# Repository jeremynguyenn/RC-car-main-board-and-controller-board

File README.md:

| Control Board
 | Main RC board

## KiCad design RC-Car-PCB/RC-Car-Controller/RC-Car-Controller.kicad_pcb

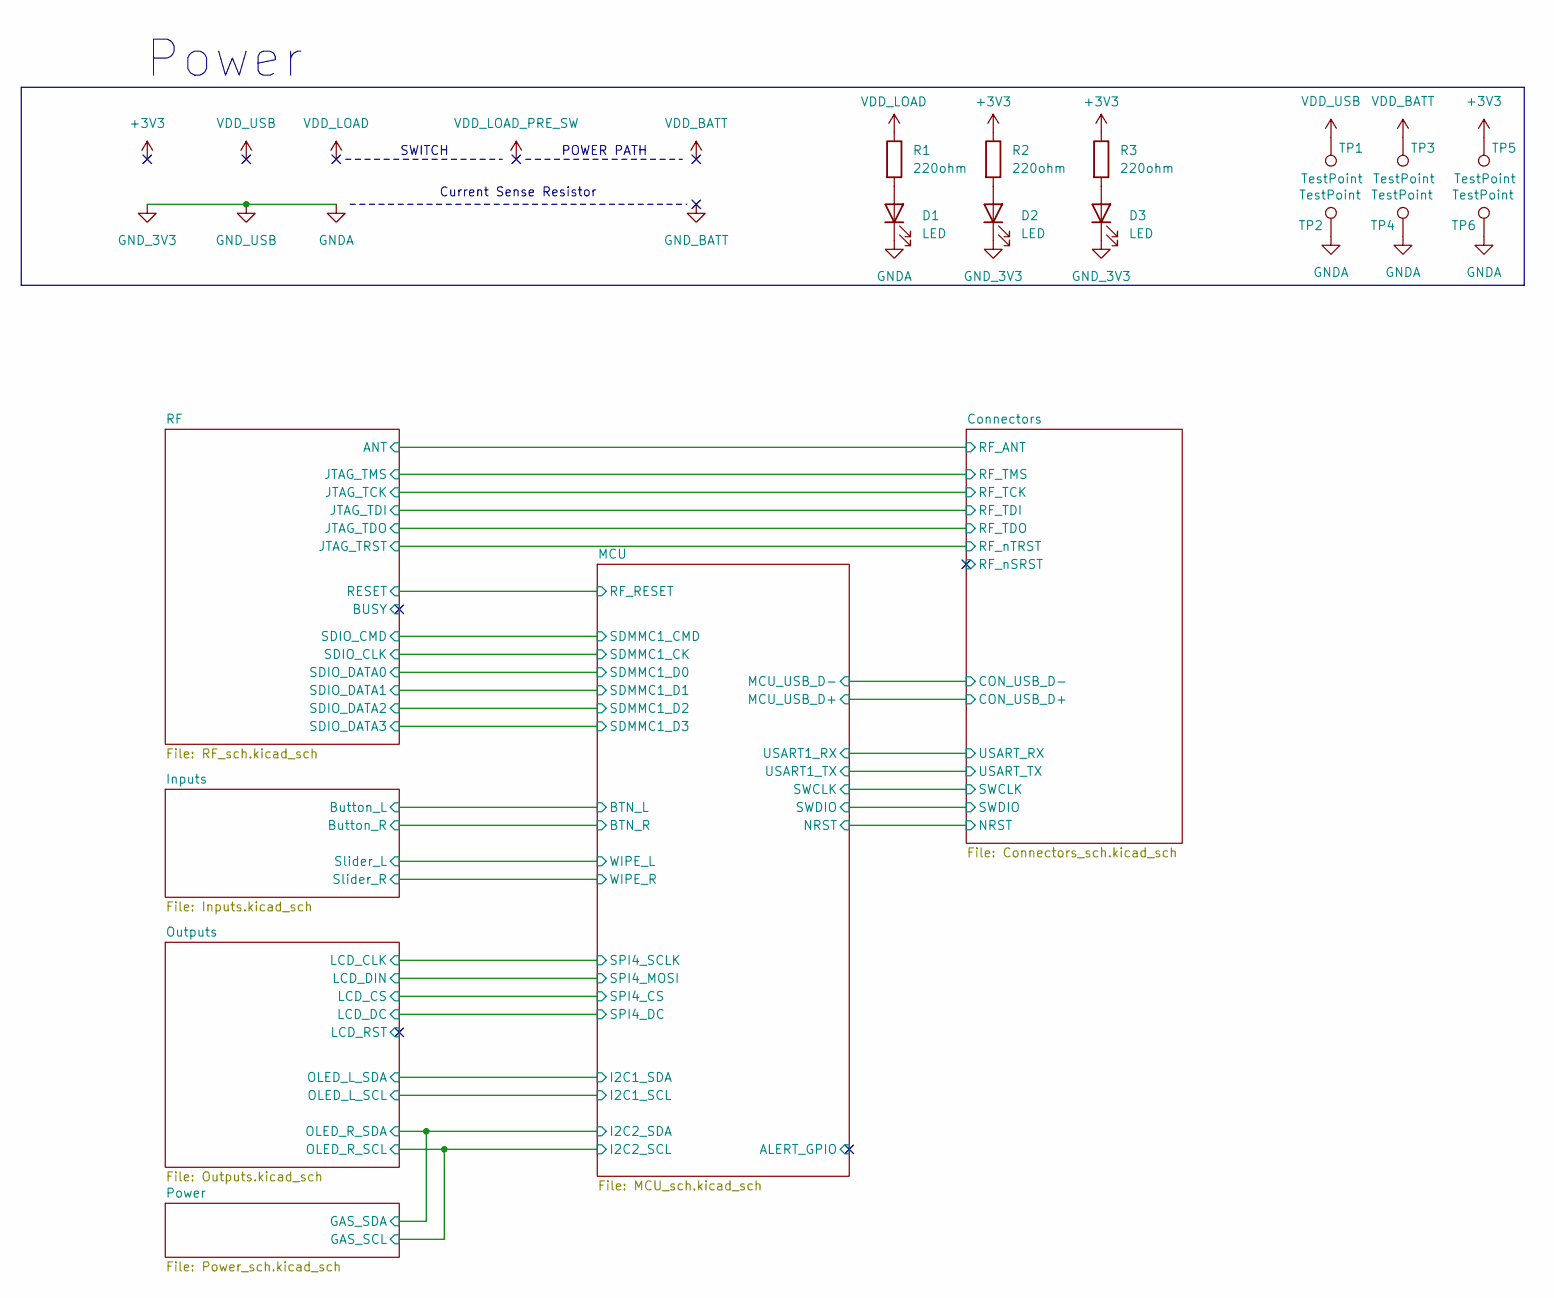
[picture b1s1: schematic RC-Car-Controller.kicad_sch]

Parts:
D1, D2: LED; LED_0603_1608Metric; MANUF_PN LTST-C190GKT
D3: LED; LED_D5.0mm; MANUF_PN LTL-4293
R1, R2, R3: 220ohm; R_0603_1608Metric; MANUF_PN RMCF0603FT220R
TP1, TP2, TP3, TP4, TP5, TP6: TestPoint; PinHeader_1x02_P2.54mm_Vertical; MANUF_PN N/A

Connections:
+3V3: R2.1, R3.1, TP5.1; also elsewhere on the board
GNDA: D1.1 (K), D2.1 (K), D3.1 (K), TP2.1, TP4.1, TP6.1; also elsewhere on the board
unnamed: D1.2 (A), R1.2
unnamed: D2.2 (A), R2.2
unnamed: D3.2 (A), R3.2
VDD_BATT: TP3.1; also elsewhere on the board
VDD_LOAD: R1.1; also elsewhere on the board
VDD_USB: TP1.1; also elsewhere on the board

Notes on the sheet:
Power
POWER PATH
Current Sense Resistor
SWITCH

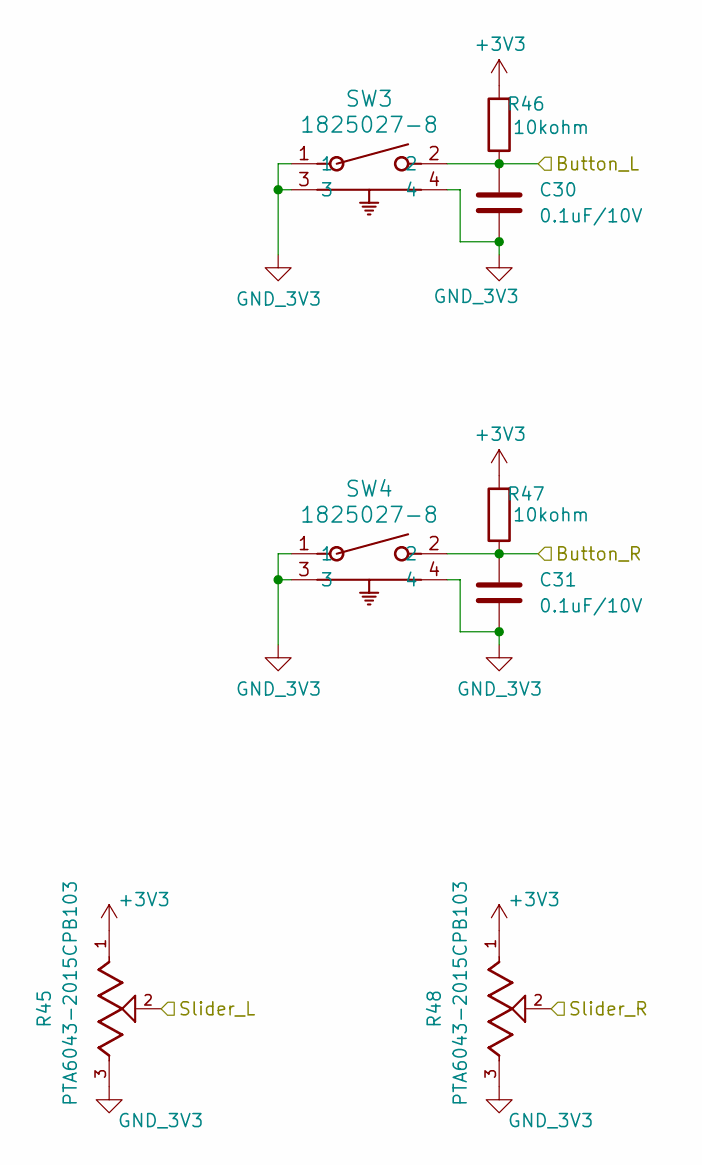
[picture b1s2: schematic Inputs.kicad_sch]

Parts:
C30, C31: 0.1uF/10V; C_0603_1608Metric; MANUF_PN C0603C104K5RAC7411
R45, R48: PTA6043-2015CPB103; Potentiometer_Bourns_PTA6043_Single_Slide; MANUF_PN PTA6043-2015CPB103
R46, R47: 10kohm; C_0603_1608Metric; MANUF_PN RC0603FR-0710KL
SW3, SW4: 1825027-8; SW2_1825027-C_TEC; MANUF_PN 1825027-8

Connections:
+3V3: R45.1, R46.2, R47.2, R48.1; also elsewhere on the board
/Inputs/Button_L: C30.1, R46.1, SW3.2; also elsewhere on the board
/Inputs/Button_R: C31.1, R47.1, SW4.2; also elsewhere on the board
/Inputs/Slider_L: R45.2; also elsewhere on the board
/Inputs/Slider_R: R48.2; also elsewhere on the board
GNDA: C30.2, C31.2, R45.3, R48.3, SW3.1, SW3.3, SW3.4, SW4.1, SW4.3, SW4.4; also elsewhere on the board

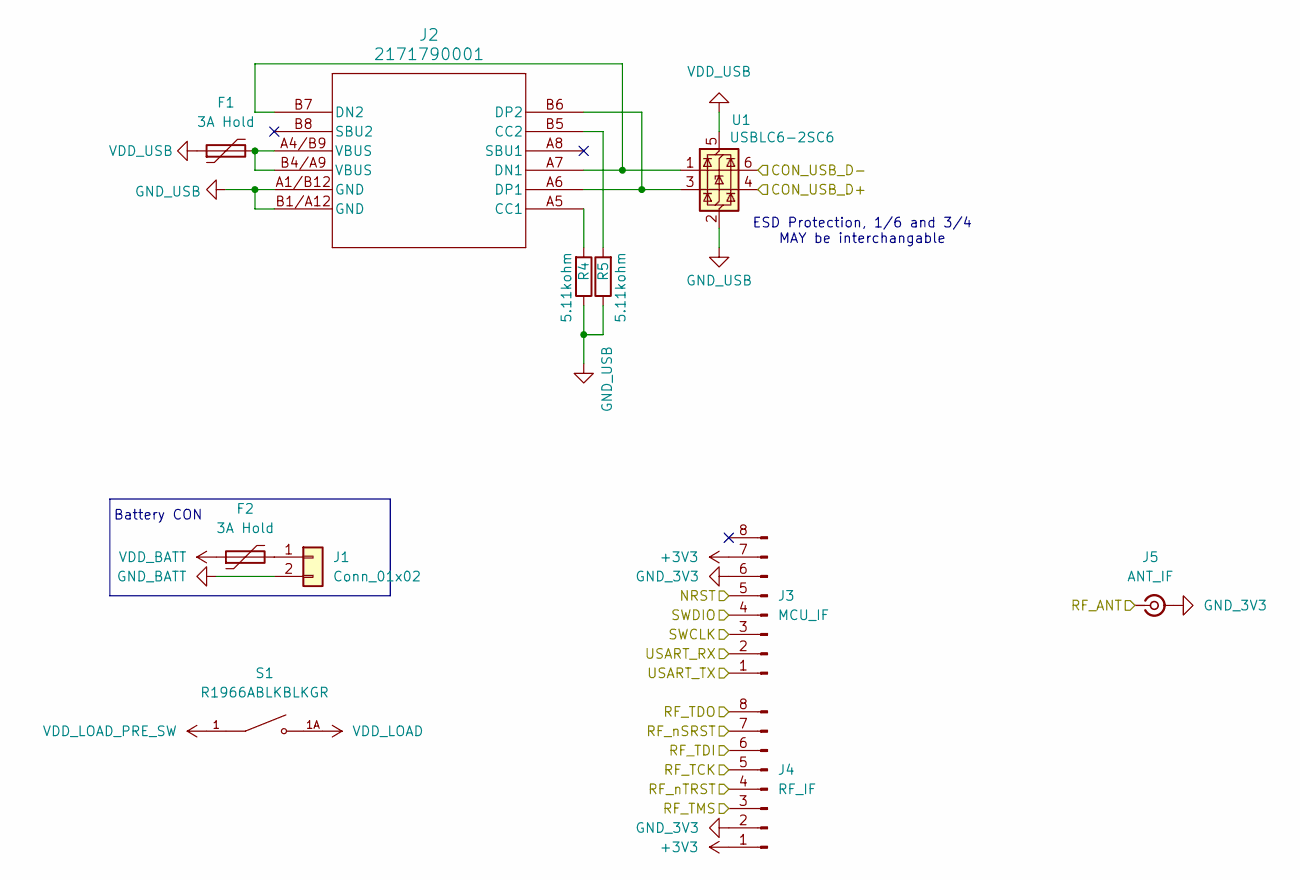
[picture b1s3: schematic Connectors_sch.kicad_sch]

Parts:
F1, F2: 3A Hold; Fuse_1812_4532Metric_Pad1.30x3.40mm_HandSolder; MANUF_PN 0ZCG0300FF2B
J1: Conn_01x02; JST_XH_B2B-XH-AM_1x02_P2.50mm_Vertical; MANUF_PN B2B-XH-AM
J2: 2171790001; 2171790001_MOL; MANUF_PN 2171790001
J3: MCU_IF; PinHeader_2x04_P2.54mm_Vertical; MANUF_PN PH2-08-UA
J4: RF_IF; PinHeader_2x04_P2.54mm_Vertical; MANUF_PN PH2-08-UA
J5: ANT_IF; SMA_Molex_73251-1153_EdgeMount_Horizontal; MANUF_PN 0732511153
R4, R5: 5.11kohm; R_0603_1608Metric; MANUF_PN CRCW06035K11FKEAC
S1: R1966ABLKBLKGR; SW_R1966ABLKBLKGR; PARTREV E
U1: USBLC6-2SC6; SOT-23-6; MANUF_PN USBLC6-2SC6

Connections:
+3V3: J3.7, J4.1; also elsewhere on the board
/Connectors/CON_USB_D+: U1.4 (I/O2); also elsewhere on the board
/Connectors/CON_USB_D-: U1.6 (I/O1); also elsewhere on the board
/Connectors/NRST: J3.5; also elsewhere on the board
/Connectors/RF_ANT: J5.1 (In); also elsewhere on the board
/Connectors/RF_TCK: J4.5; also elsewhere on the board
/Connectors/RF_TDI: J4.6; also elsewhere on the board
/Connectors/RF_TDO: J4.8; also elsewhere on the board
/Connectors/RF_TMS: J4.3; also elsewhere on the board
/Connectors/RF_nSRST: J4.7
/Connectors/RF_nTRST: J4.4; also elsewhere on the board
/Connectors/SWCLK: J3.3; also elsewhere on the board
/Connectors/SWDIO: J3.4; also elsewhere on the board
/Connectors/USART_RX: J3.2; also elsewhere on the board
/Connectors/USART_TX: J3.1; also elsewhere on the board
GNDA: J2.A1/B12 (GND), J2.B1/A12 (GND), J3.6, J4.2, J5.2 (Ext), R4.1, R5.1, U1.2 (GND); also elsewhere on the board
GND_BATT: J1.2; also elsewhere on the board
unnamed: F1.2, J2.A4/B9 (VBUS), J2.B4/A9 (VBUS)
unnamed: F2.2, J1.1
unnamed: J2.A5 (CC1), R4.2
unnamed: J2.B5 (CC2), R5.2
unnamed: J2.A7 (DN1), J2.B7 (DN2), U1.1 (I/O1)
unnamed: J2.A6 (DP1), J2.B6 (DP2), U1.3 (I/O2)
VDD_BATT: F2.1; also elsewhere on the board
VDD_LOAD: S1.1A; also elsewhere on the board
VDD_LOAD_PRE_SW: S1.1; also elsewhere on the board
VDD_USB: F1.1, U1.5 (VBUS); also elsewhere on the board

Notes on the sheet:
Battery CON
ESD Protection, 1/6 and 3/4 MAY be interchangable

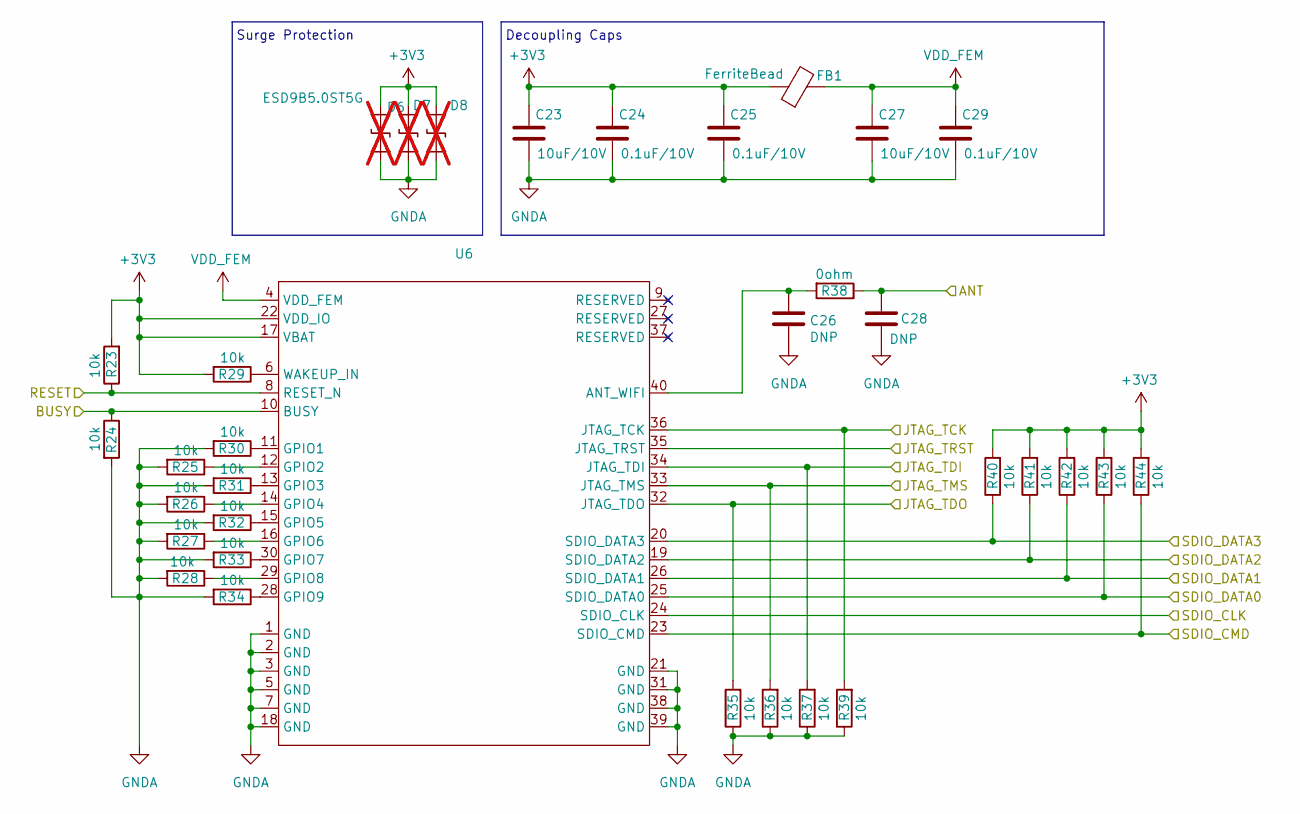
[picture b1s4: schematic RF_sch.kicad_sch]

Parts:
C23, C27: 10uF/10V; C_0603_1608Metric; MANUF_PN CL10A106KP8NNNC
C24, C25, C29: 0.1uF/10V; C_0603_1608Metric; MANUF_PN C0603C104K5RAC7411
C26, C28: DNP; C_0603_1608Metric; MANUF_PN N/A
D6, D7, D8: ESD9B5.0ST5G; D_SOD-923; MANUF_PN ESD9B5.0ST5G; not fitted
FB1: FerriteBead; C_0603_1608Metric; MANUF_PN HCB 1608KF-181T20
R23, R24, R25, R26, R27, R28, R29, R30, R31, R32, R33, R34, R35, R36, R37, R39, R40, R41, R42, R43, R44: 10k; C_0603_1608Metric; MANUF_PN RC0603FR-0710KL
R38: 0ohm; R_0603_1608Metric; MANUF_PN RMCF0603ZT0R00
U6: FGH100MABMD; MANUF_PN FGH100MABMD

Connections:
+3V3: C23.1, C24.1, C25.1, D6.2 (A2), D7.2 (A2), D8.2 (A2), FB1.1, R23.2, R29.2, R40.2, R41.2, R42.2, R43.2, R44.2, U6.17 (VBAT), U6.22 (VDD_IO); also elsewhere on the board
/Connectors/RF_ANT: C28.1, R38.1; also elsewhere on the board
/Connectors/RF_TCK: R39.2, U6.36 (JTAG_TCK); also elsewhere on the board
/Connectors/RF_TDI: R37.2, U6.34 (JTAG_TDI); also elsewhere on the board
/Connectors/RF_TDO: R35.2, U6.32 (JTAG_TDO); also elsewhere on the board
/Connectors/RF_TMS: R36.2, U6.33 (JTAG_TMS); also elsewhere on the board
/Connectors/RF_nTRST: U6.35 (JTAG_TRST); also elsewhere on the board
/MCU/RF_RESET: R23.1, U6.8 (RESET_N); also elsewhere on the board
/MCU/SDMMC1_CK: U6.24 (SDIO_CLK); also elsewhere on the board
/MCU/SDMMC1_CMD: R44.1, U6.23 (SDIO_CMD); also elsewhere on the board
/MCU/SDMMC1_D0: R43.1, U6.25 (SDIO_DATA0); also elsewhere on the board
/MCU/SDMMC1_D1: R42.1, U6.26 (SDIO_DATA1); also elsewhere on the board
/MCU/SDMMC1_D2: R41.1, U6.19 (SDIO_DATA2); also elsewhere on the board
/MCU/SDMMC1_D3: R40.1, U6.20 (SDIO_DATA3); also elsewhere on the board
/RF/BUSY: R24.1, U6.10 (BUSY)
GNDA: C23.2, C24.2, C25.2, C26.2, C27.2, C28.2, C29.2, D6.1 (A1), D7.1 (A1), D8.1 (A1), R24.2, R25.2, R26.2, R27.2, R28.2, R30.2, R31.2, R32.2, R33.2, R34.2, R35.1, R36.1, R37.1, R39.1, U6.1 (GND), U6.2 (GND), U6.3 (GND), U6.5 (GND), U6.7 (GND), U6.18 (GND), U6.21 (GND), U6.31 (GND), U6.38 (GND), U6.39 (GND); also elsewhere on the board
unnamed: C26.1, R38.2, U6.40 (ANT_WIFI)
unnamed: R30.1, U6.11 (GPIO1)
unnamed: R25.1, U6.12 (GPIO2)
unnamed: R31.1, U6.13 (GPIO3)
unnamed: R26.1, U6.14 (GPIO4)
unnamed: R32.1, U6.15 (GPIO5)
unnamed: R27.1, U6.16 (GPIO6)
unnamed: R33.1, U6.30 (GPIO7)
unnamed: R28.1, U6.29 (GPIO8)
unnamed: R34.1, U6.28 (GPIO9)
unnamed: R29.1, U6.6 (WAKEUP_IN)
VDD_FEM: C27.1, C29.1, FB1.2, U6.4 (VDD_FEM)

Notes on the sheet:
Decoupling Caps
Surge Protection

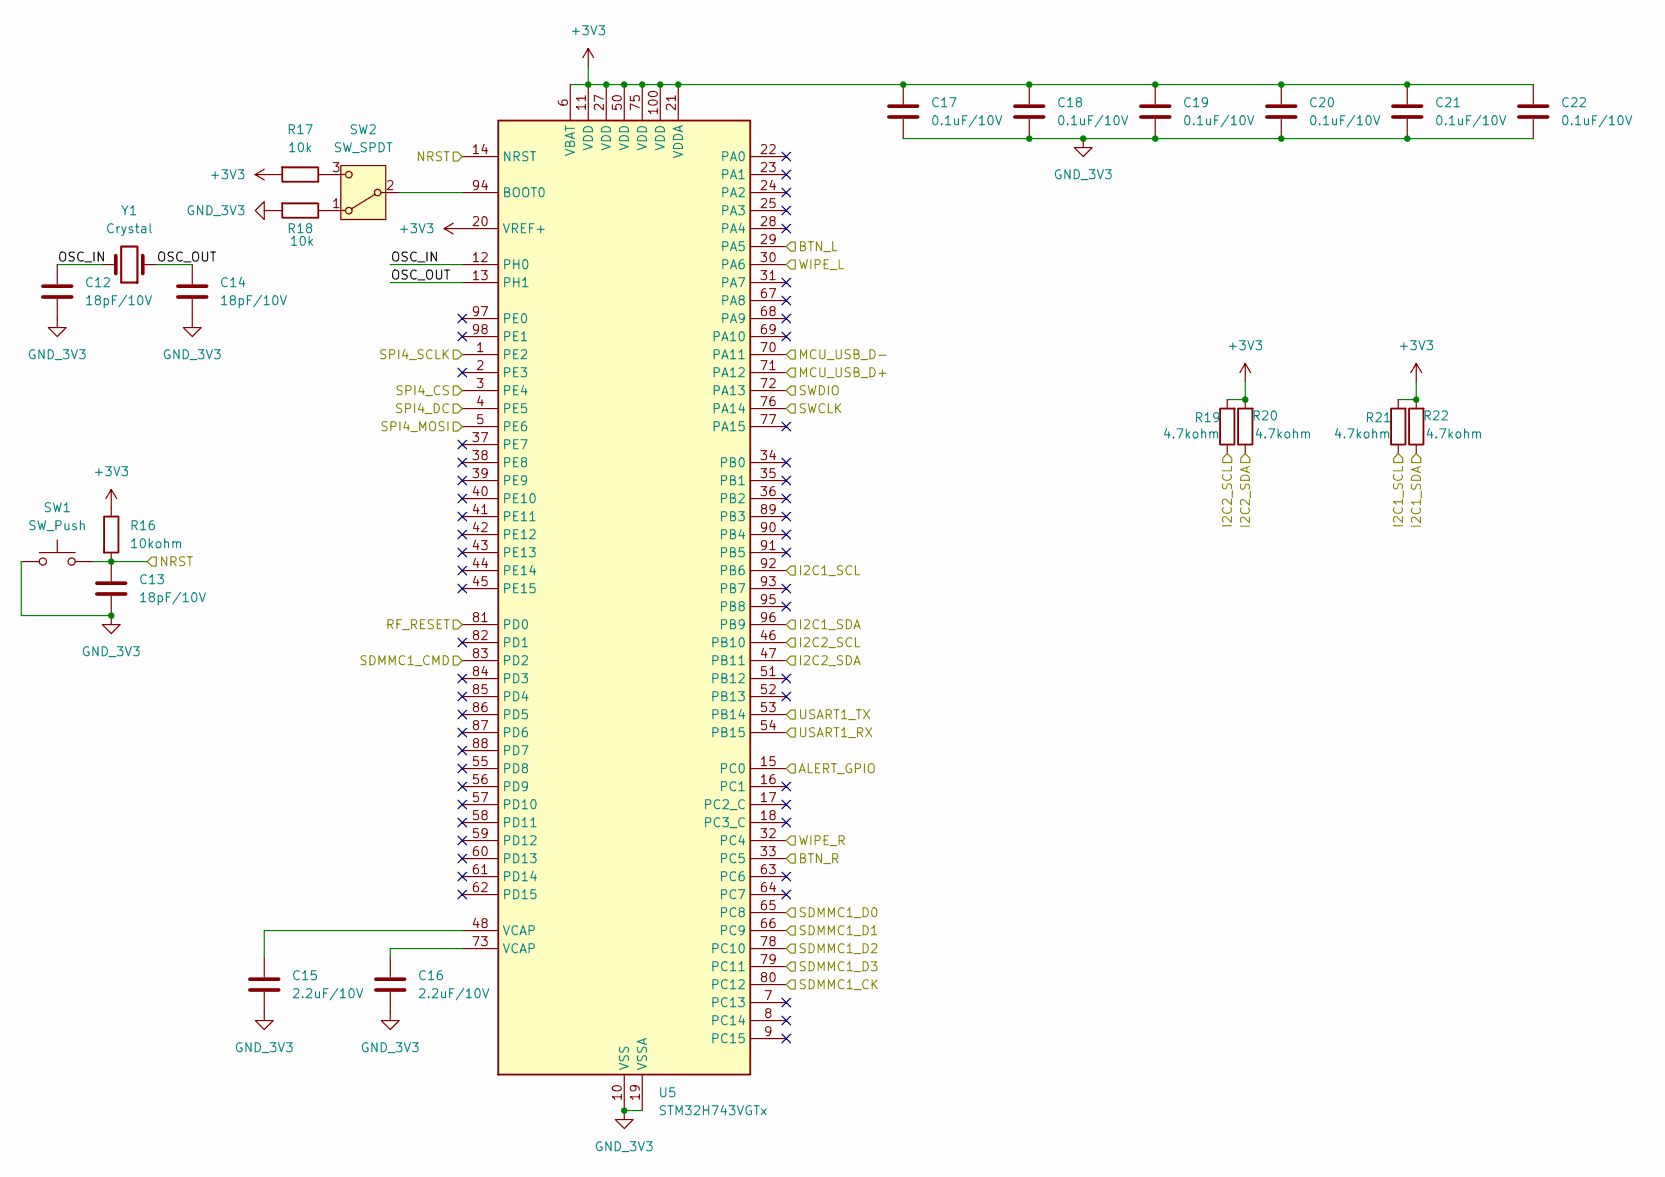
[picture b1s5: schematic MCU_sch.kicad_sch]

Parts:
C12, C13, C14: 18pF/10V; C_0603_1608Metric; MANUF_PN C0603C180J5GACTU
C15, C16: 2.2uF/10V; C_0603_1608Metric; MANUF_PN C0603C225K4PACTU
C17, C18, C19, C20, C21, C22: 0.1uF/10V; C_0603_1608Metric; MANUF_PN C0603C104K5RAC7411
R16: 10kohm; C_0603_1608Metric; MANUF_PN RC0603FR-0710KL
R17, R18: 10k; C_0603_1608Metric; MANUF_PN RC0603FR-0710KL
R19, R20, R21, R22: 4.7kohm; R_0603_1608Metric; MANUF_PN ERA-3ARW472V
SW1: SW_Push; SW_SPST_Omron_B3F-40xx; MANUF_PN 1825910-6
SW2: SW_SPDT; PinHeader_1x03_P2.54mm_Vertical; MANUF_PN N/A
U5: STM32H743VGTx; LQFP-100_14x14mm_P0.5mm; MANUF_PN STM32H743VGT6
Y1: Crystal; Crystal_SMD_Abracon_ABM3-2Pin_5.0x3.2mm; MANUF_PN ABM7-25.000MHZ-D2Y-T

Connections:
+3V3: C17.1, C18.1, C19.1, C20.1, C21.1, C22.1, R16.1, R17.2, R19.2, R20.2, R21.2, R22.2, U5.6 (VBAT), U5.11 (VDD), U5.20 (VREF+), U5.21 (VDDA), U5.27 (VDD), U5.50 (VDD), U5.75 (VDD), U5.100 (VDD); also elsewhere on the board
/Connectors/CON_USB_D+: U5.71 (PA12); also elsewhere on the board
/Connectors/CON_USB_D-: U5.70 (PA11); also elsewhere on the board
/Connectors/NRST: C13.1, R16.2, SW1.2, U5.14 (NRST); also elsewhere on the board
/Connectors/SWCLK: U5.76 (PA14); also elsewhere on the board
/Connectors/SWDIO: U5.72 (PA13); also elsewhere on the board
/Connectors/USART_RX: U5.54 (PB15); also elsewhere on the board
/Connectors/USART_TX: U5.53 (PB14); also elsewhere on the board
/Inputs/Button_L: U5.29 (PA5); also elsewhere on the board
/Inputs/Button_R: U5.33 (PC5); also elsewhere on the board
/Inputs/Slider_L: U5.30 (PA6); also elsewhere on the board
/Inputs/Slider_R: U5.32 (PC4); also elsewhere on the board
/MCU/ALERT_GPIO: U5.15 (PC0)
/MCU/I2C1_SCL: R21.1, U5.92 (PB6); also elsewhere on the board
/MCU/I2C1_SDA: R22.1, U5.96 (PB9); also elsewhere on the board
/MCU/I2C2_SCL: R19.1, U5.46 (PB10); also elsewhere on the board
/MCU/I2C2_SDA: R20.1, U5.47 (PB11); also elsewhere on the board
/MCU/OSC_IN: C12.1, U5.12 (PH0), Y1.2
/MCU/OSC_OUT: C14.1, U5.13 (PH1), Y1.1
/MCU/RF_RESET: U5.81 (PD0); also elsewhere on the board
/MCU/SDMMC1_CK: U5.80 (PC12); also elsewhere on the board
/MCU/SDMMC1_CMD: U5.83 (PD2); also elsewhere on the board
/MCU/SDMMC1_D0: U5.65 (PC8); also elsewhere on the board
/MCU/SDMMC1_D1: U5.66 (PC9); also elsewhere on the board
/MCU/SDMMC1_D2: U5.78 (PC10); also elsewhere on the board
/MCU/SDMMC1_D3: U5.79 (PC11); also elsewhere on the board
/MCU/SPI4_CS: U5.3 (PE4); also elsewhere on the board
/MCU/SPI4_DC: U5.4 (PE5); also elsewhere on the board
/MCU/SPI4_MOSI: U5.5 (PE6); also elsewhere on the board
/MCU/SPI4_SCLK: U5.1 (PE2); also elsewhere on the board
GNDA: C12.2, C13.2, C14.2, C15.2, C16.2, C17.2, C18.2, C19.2, C20.2, C21.2, C22.2, R18.2, SW1.1, U5.10 (VSS), U5.19 (VSSA), U5.26 (VSS), U5.49 (VSS), U5.74 (VSS), U5.99 (VSS); also elsewhere on the board
unnamed: C15.1, U5.48 (VCAP)
unnamed: C16.1, U5.73 (VCAP)
unnamed: R18.1, SW2.1 (A)
unnamed: SW2.2 (B), U5.94 (BOOT0)
unnamed: R17.1, SW2.3 (C)

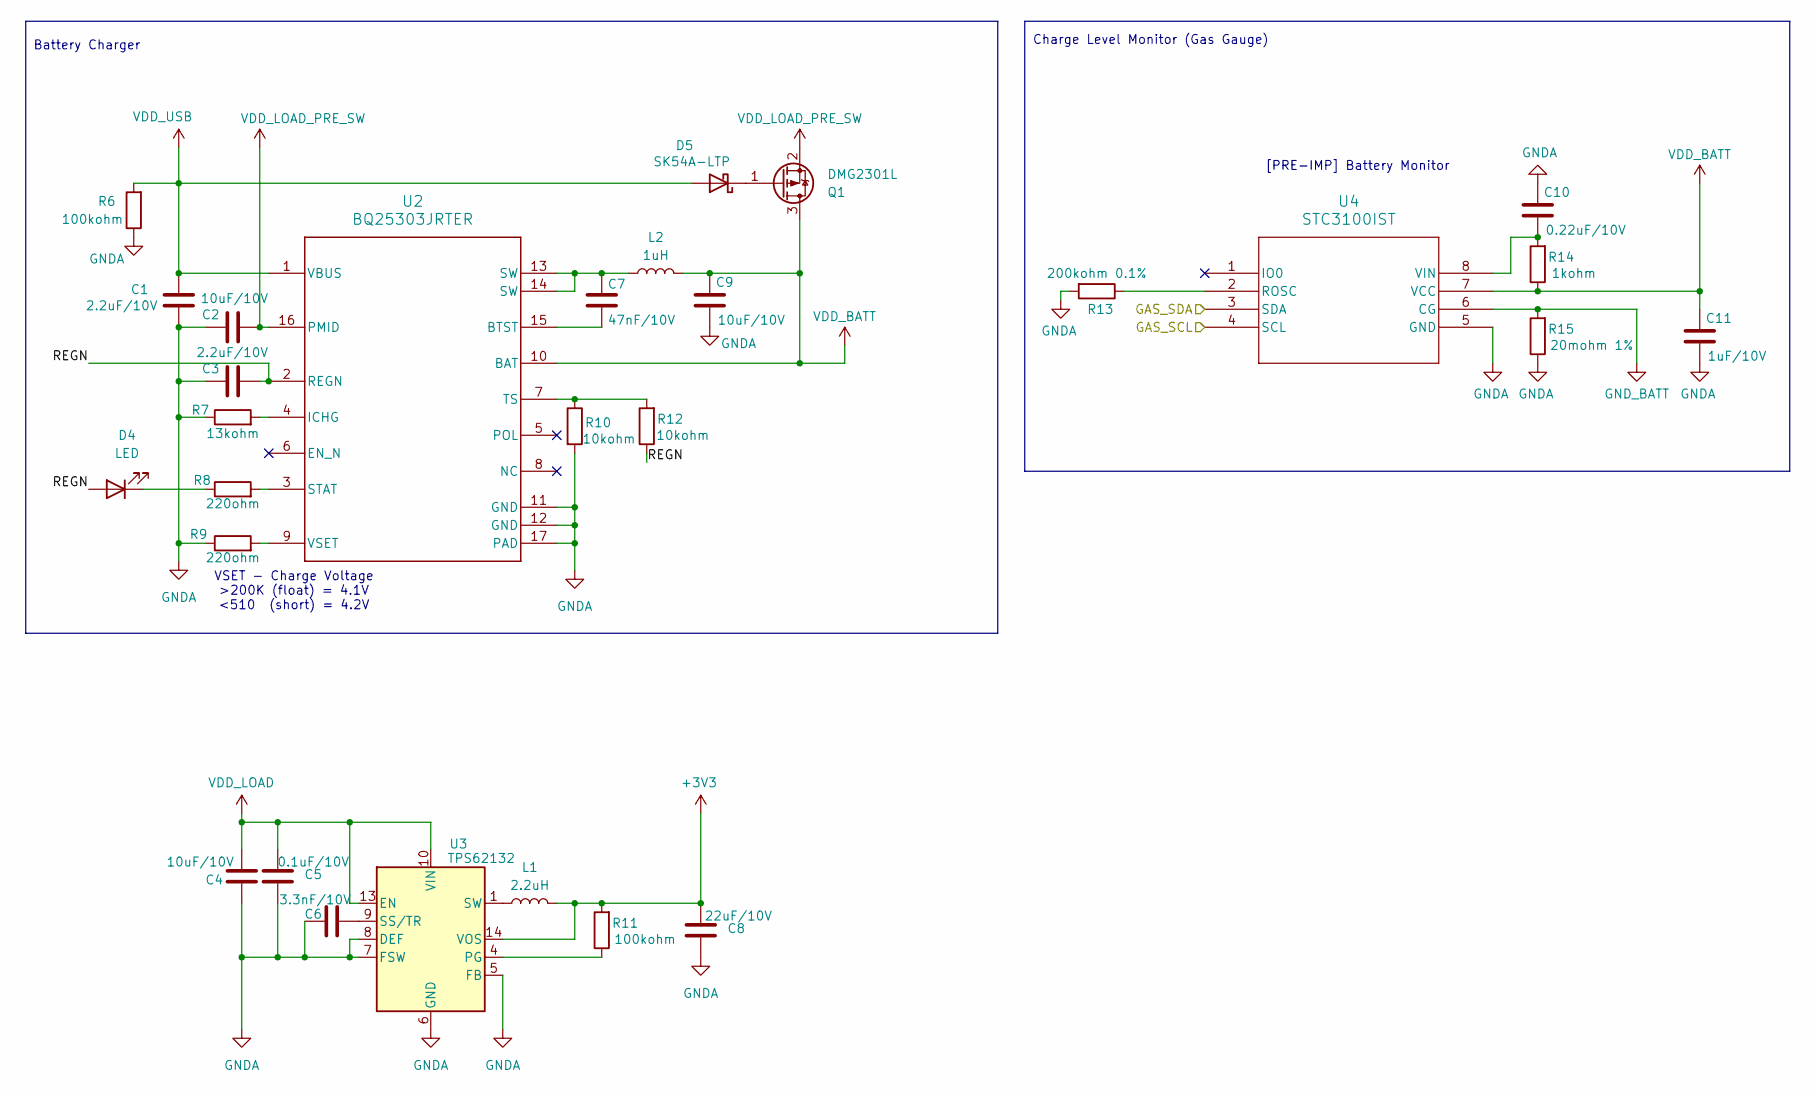
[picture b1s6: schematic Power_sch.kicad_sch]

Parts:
C1, C3: 2.2uF/10V; C_0603_1608Metric; MANUF_PN C0603C225K4PACTU
C2, C9: 10uF/10V; C_0603_1608Metric; MANUF_PN CL10A106KP8NNNC
C4: 10uF/10V; C_1210_3225Metric; MANUF_PN LMK325B7106KN-T
C5: 0.1uF/10V; C_0603_1608Metric; MANUF_PN C0603C104K5RAC7411
C6: 3.3nF/10V; C_0603_1608Metric; MANUF_PN 885012206011
C7: 47nF/10V; C_0603_1608Metric; MANUF_PN 885012206018
C8: 22uF/10V; C_0805_2012Metric; MANUF_PN CL21A226MPQNNNE
C10: 0.22uF/10V; C_0603_1608Metric; MANUF_PN CC0603KRX7R6BB224
C11: 1uF/10V; C_0603_1608Metric; MANUF_PN CL10B105KO8NNNC
D4: LED; LED_0603_1608Metric; MANUF_PN LTST-C190GKT
D5: SK54A-LTP; D_SMA; MANUF_PN SK54A-LTP
L1: 2.2uH; L_Wuerth_MAPI-4030; MANUF_PN 74438357022
L2: 1uH; L_Wuerth_MAPI-4030; MANUF_PN 74438357010
Q1: DMG2301L; SOT-23; MANUF_PN DMG2301L-7
R6, R11: 100kohm; R_0603_1608Metric; MANUF_PN RMCF0603FT100K
R7: 13kohm; R_0603_1608Metric; MANUF_PN RC0603FR-0713KL
R8, R9: 220ohm; R_0603_1608Metric; MANUF_PN RMCF0603FT220R
R10, R12: 10kohm; C_0603_1608Metric; MANUF_PN RC0603FR-0710KL
R13: 200kohm 0.1%; R_0603_1608Metric; MANUF_PN RG1608N-204-W-T1
R14: 1kohm; R_0603_1608Metric; MANUF_PN RMCF0603FT1K00
R15: 20mohm 1%; R_0805_2012Metric; MANUF_PN ERJ-6CWDR020V
U2: BQ25303JRTER; RTE0016C; MANUF_PN BQ25303JRTER
U3: TPS62132; VQFN-16-1EP_3x3mm_P0.5mm_EP1.68x1.68mm_ThermalVias; MANUF_PN TPS62132RGTR
U4: STC3100IST; MiniSO8_STM; MANUF_PN STC3100IST

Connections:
+3V3: C8.2, L1.2, R11.2, U3.14 (VOS); also elsewhere on the board
/MCU/I2C2_SCL: U4.4 (SCL); also elsewhere on the board
/MCU/I2C2_SDA: U4.3 (SDA); also elsewhere on the board
/Power/REGN: C3.2, D4.2 (A), R12.1, U2.2 (REGN)
GNDA: C1.2, C2.1, C3.1, C4.1, C5.1, C6.1, C8.1, C9.2, C10.1, C11.2, R6.1, R7.1, R9.1, R10.2, R13.2, R15.1, U2.11 (GND), U2.12 (GND), U2.17 (PAD), U3.5 (FB), U3.6 (GND), U3.7 (FSW), U3.8 (DEF), U3.15 (GND), U3.16 (GND), U3.17 (GND), U4.5 (GND); also elsewhere on the board
GND_BATT: R15.2, U4.6 (CG); also elsewhere on the board
unnamed: C7.1, L2.1, U2.13 (SW), U2.14 (SW)
unnamed: D4.1 (K), R8.1
unnamed: D5.1 (K), Q1.1 (G)
unnamed: L1.1, U3.1 (SW), U3.2 (SW), U3.3 (SW)
unnamed: C7.2, U2.15 (BTST)
unnamed: R7.2, U2.4 (ICHG)
unnamed: R8.2, U2.3 (STAT)
unnamed: R10.1, R12.2, U2.7 (TS)
unnamed: R9.2, U2.9 (VSET)
unnamed: R11.1, U3.4 (PG)
unnamed: C6.2, U3.9 (SS/TR)
unnamed: R13.1, U4.2 (ROSC)
unnamed: C10.2, R14.2, U4.8 (VIN)
VDD_BATT: C9.1, C11.1, L2.2, Q1.3 (D), R14.1, U2.10 (BAT), U4.7 (VCC); also elsewhere on the board
VDD_LOAD: C4.2, C5.2, U3.10 (VIN), U3.11 (VIN), U3.12 (VIN), U3.13 (EN); also elsewhere on the board
VDD_LOAD_PRE_SW: C2.2, Q1.2 (S), U2.16 (PMID); also elsewhere on the board
VDD_USB: C1.1, D5.2 (A), R6.2, U2.1 (VBUS); also elsewhere on the board

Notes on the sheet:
Battery Charger
[PRE-IMP] Battery Monitor
Charge Level Monitor (Gas Gauge)
VSET - Charge Voltage >200K (float) = 4.1V <510 (short) = 4.2V

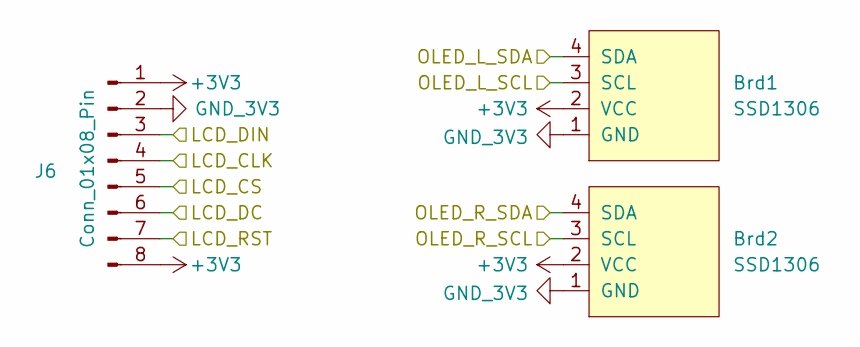
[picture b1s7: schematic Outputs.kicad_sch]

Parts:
Brd1, Brd2: SSD1306; 128x64OLED; MANUF_PN N/A
J6: Conn_01x08_Pin; 2inch_LCD; MANUF_PN N/A

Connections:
+3V3: Brd1.2 (VCC), Brd2.2 (VCC), J6.1, J6.8; also elsewhere on the board
/MCU/I2C1_SCL: Brd1.3 (SCL); also elsewhere on the board
/MCU/I2C1_SDA: Brd1.4 (SDA); also elsewhere on the board
/MCU/I2C2_SCL: Brd2.3 (SCL); also elsewhere on the board
/MCU/I2C2_SDA: Brd2.4 (SDA); also elsewhere on the board
/MCU/SPI4_CS: J6.5; also elsewhere on the board
/MCU/SPI4_DC: J6.6; also elsewhere on the board
/MCU/SPI4_MOSI: J6.3; also elsewhere on the board
/MCU/SPI4_SCLK: J6.4; also elsewhere on the board
/Outputs/LCD_RST: J6.7
GNDA: Brd1.1 (GND), Brd2.1 (GND), J6.2; also elsewhere on the board

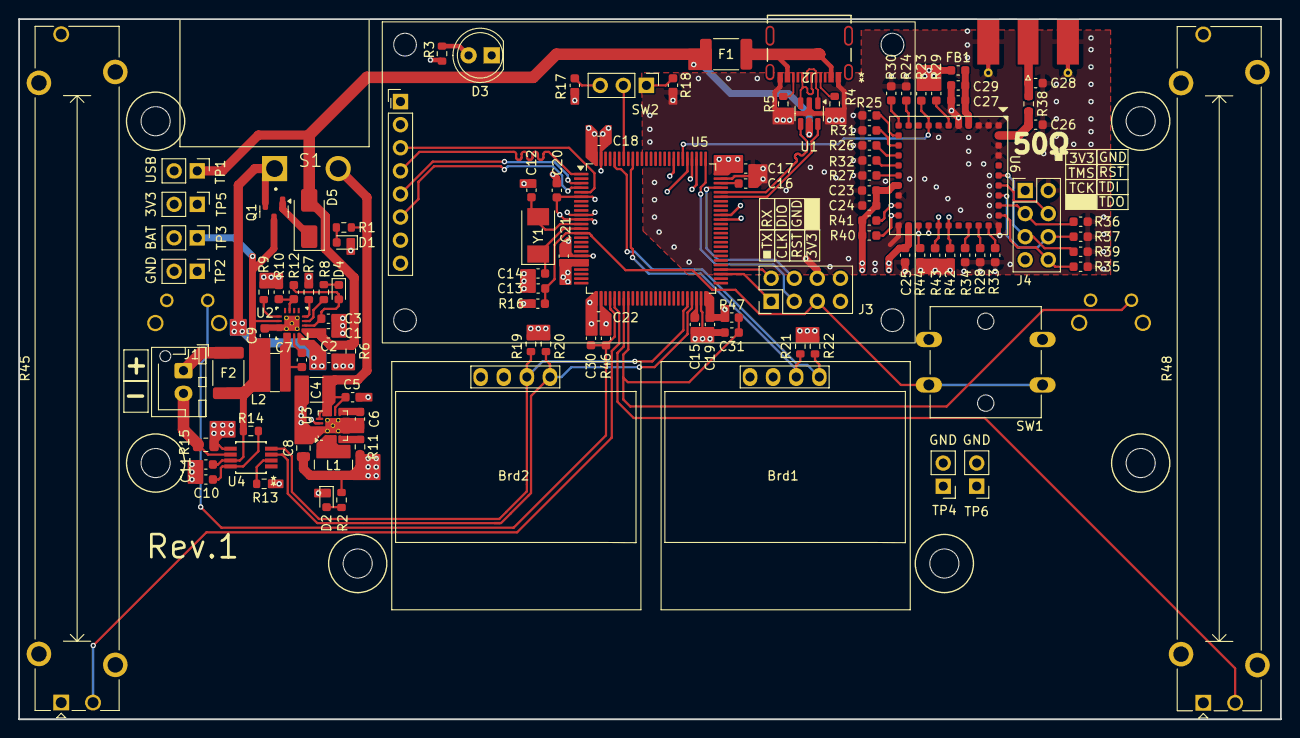
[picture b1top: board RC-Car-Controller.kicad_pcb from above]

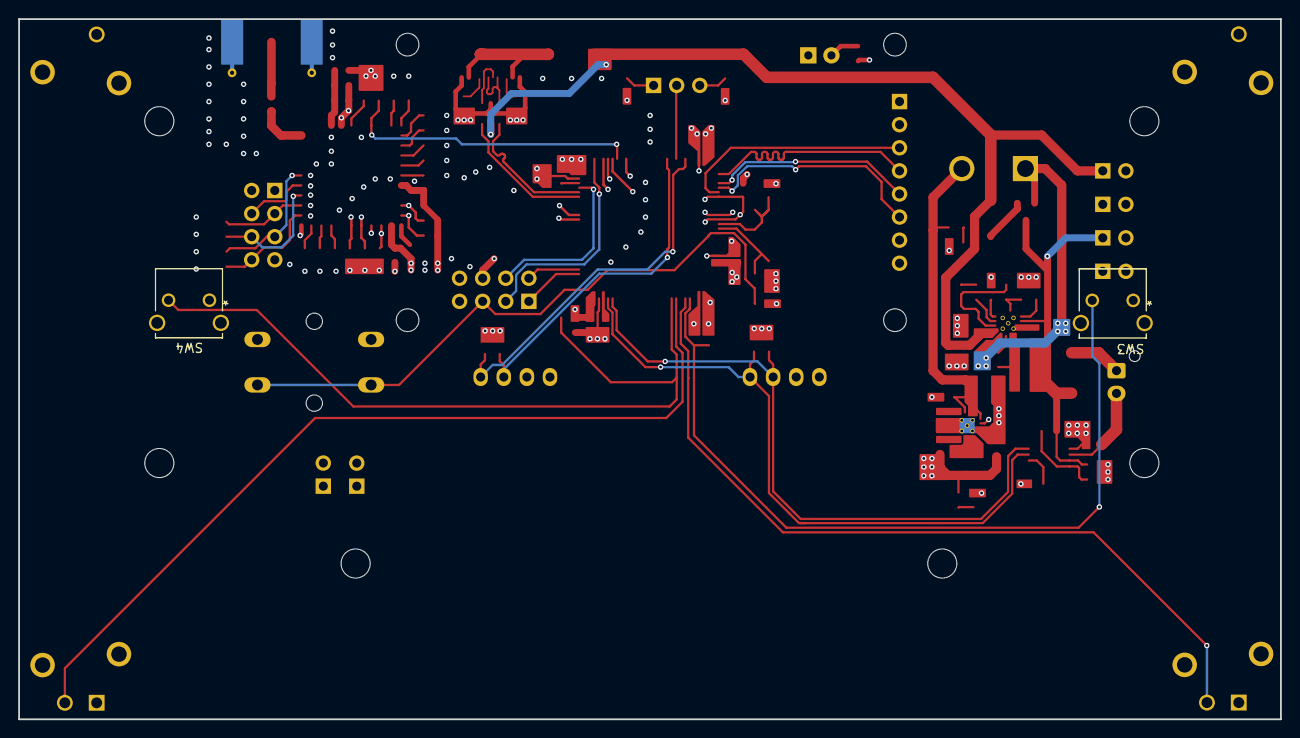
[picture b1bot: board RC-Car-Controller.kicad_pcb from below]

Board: 4 copper layers, 138.8 x 77.0 mm, 116 parts (2 on the bottom side), 82 nets.

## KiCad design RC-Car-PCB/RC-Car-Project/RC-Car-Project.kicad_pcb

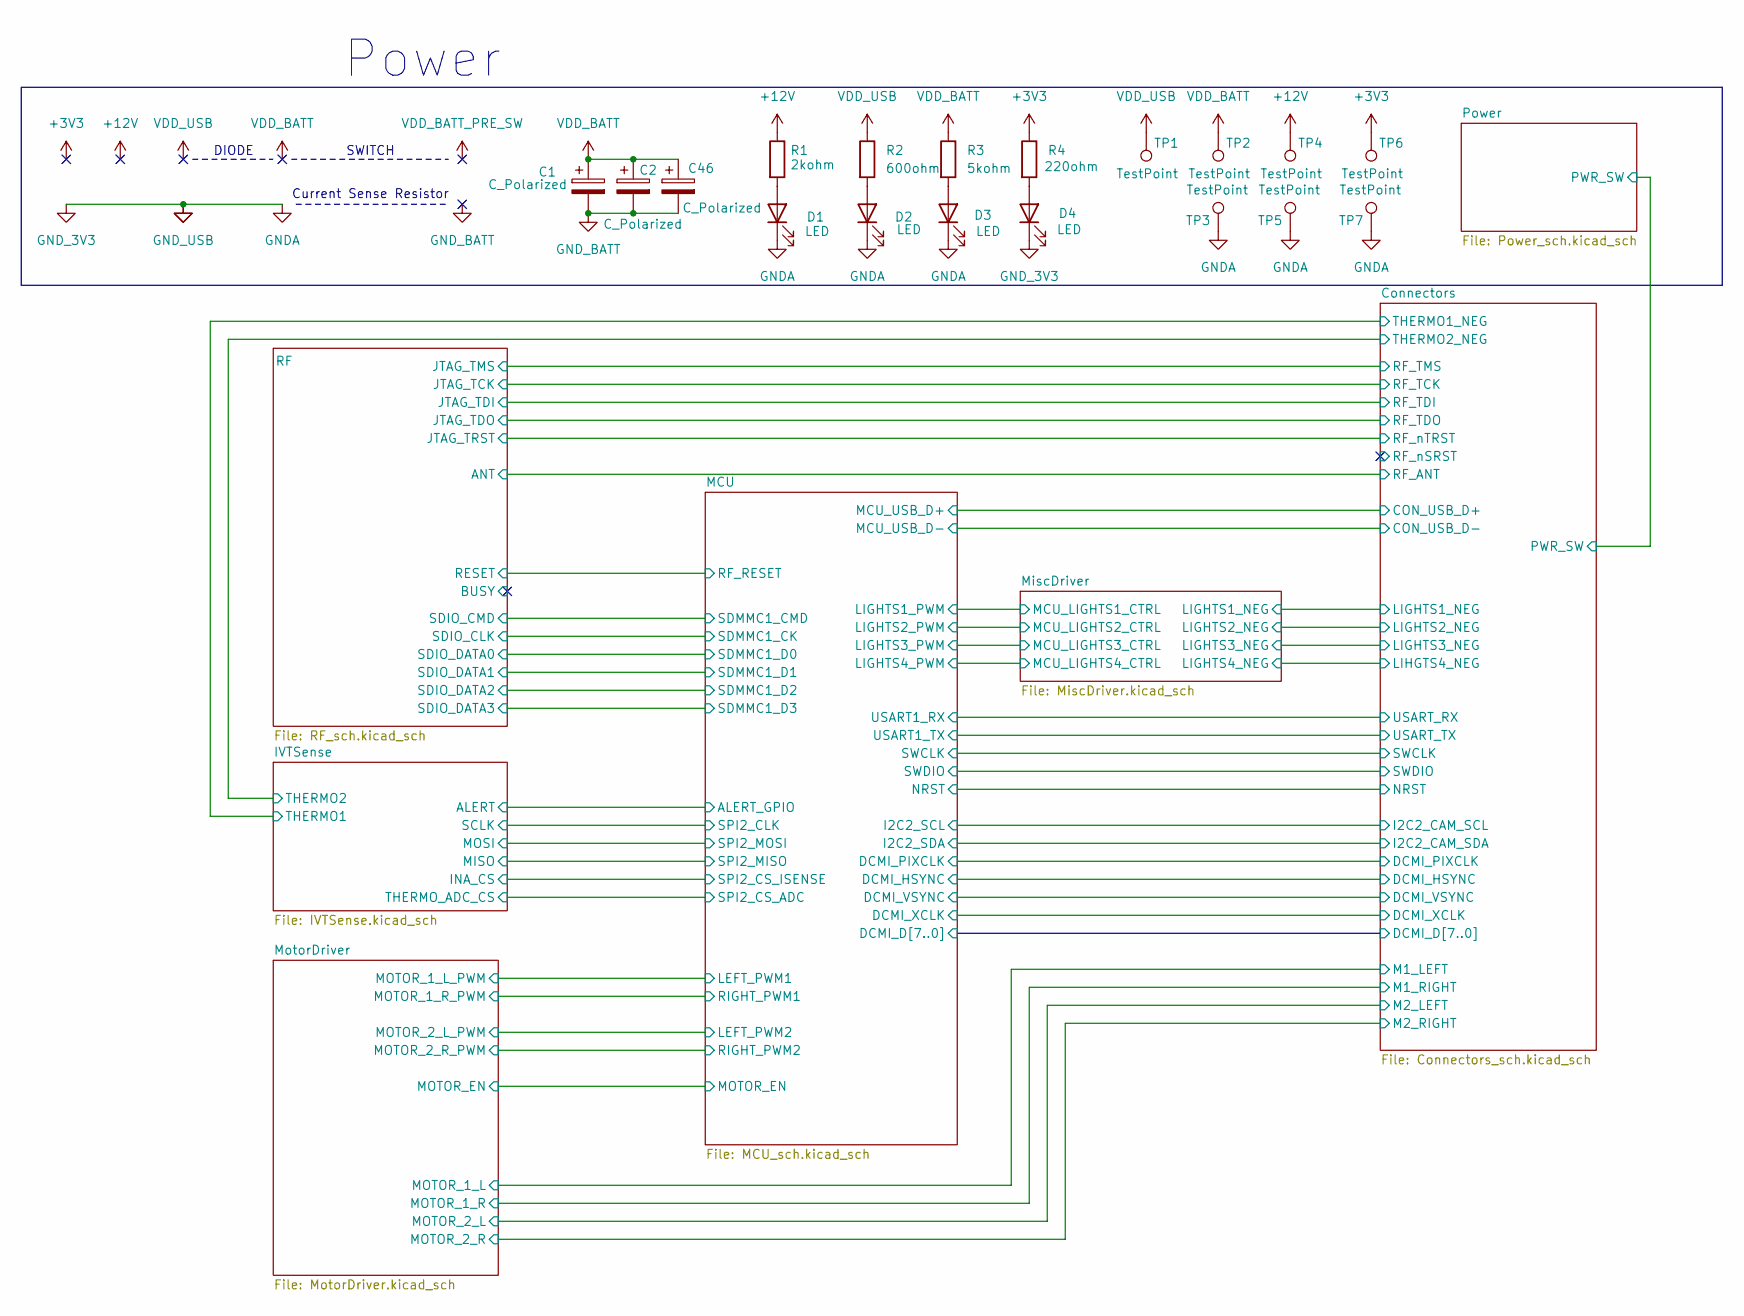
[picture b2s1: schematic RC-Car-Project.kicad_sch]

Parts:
C1, C2: C_Polarized; CP_Radial_D10.0mm_P5.00mm; MANUF_PN EEU-FS2A151LB
C46: C_Polarized; L_Radial_D12.0mm_P5.00mm_Neosid_SD12k_style2; MANUF_PN 100ZLJ330M12.5X35
D1, D2, D3, D4: LED; LED_0603_1608Metric; MANUF_PN LTST-C190GKT
R1: 2kohm; R_0603_1608Metric; MANUF_PN ERA-3AEB202V
R2: 600ohm; R_0603_1608Metric; MANUF_PN ERJ-3EKF5600V
R3: 5kohm; R_0603_1608Metric; MANUF_PN RT0603BRE075KL
R4: 220ohm; R_0603_1608Metric; MANUF_PN RMCF0603FT220R
TP1, TP2, TP3, TP4, TP5, TP6, TP7: TestPoint; PinHeader_1x02_P2.54mm_Vertical; MANUF_PN N/A

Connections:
+3V3: R4.1, TP6.1; also elsewhere on the board
+12V: R1.1, TP4.1; also elsewhere on the board
GNDA: D1.1 (K), D2.1 (K), D3.1 (K), D4.1 (K), TP3.1, TP5.1, TP7.1; also elsewhere on the board
GND_BATT: C1.2, C2.2, C46.2; also elsewhere on the board
unnamed: D1.2 (A), R1.2
unnamed: D2.2 (A), R2.2
unnamed: D3.2 (A), R3.2
unnamed: D4.2 (A), R4.2
VDD_BATT: C1.1, C2.1, C46.1, R3.1, TP2.1; also elsewhere on the board
VDD_USB: R2.1, TP1.1; also elsewhere on the board

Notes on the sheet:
DIODE
SWITCH
Current Sense Resistor
Power
